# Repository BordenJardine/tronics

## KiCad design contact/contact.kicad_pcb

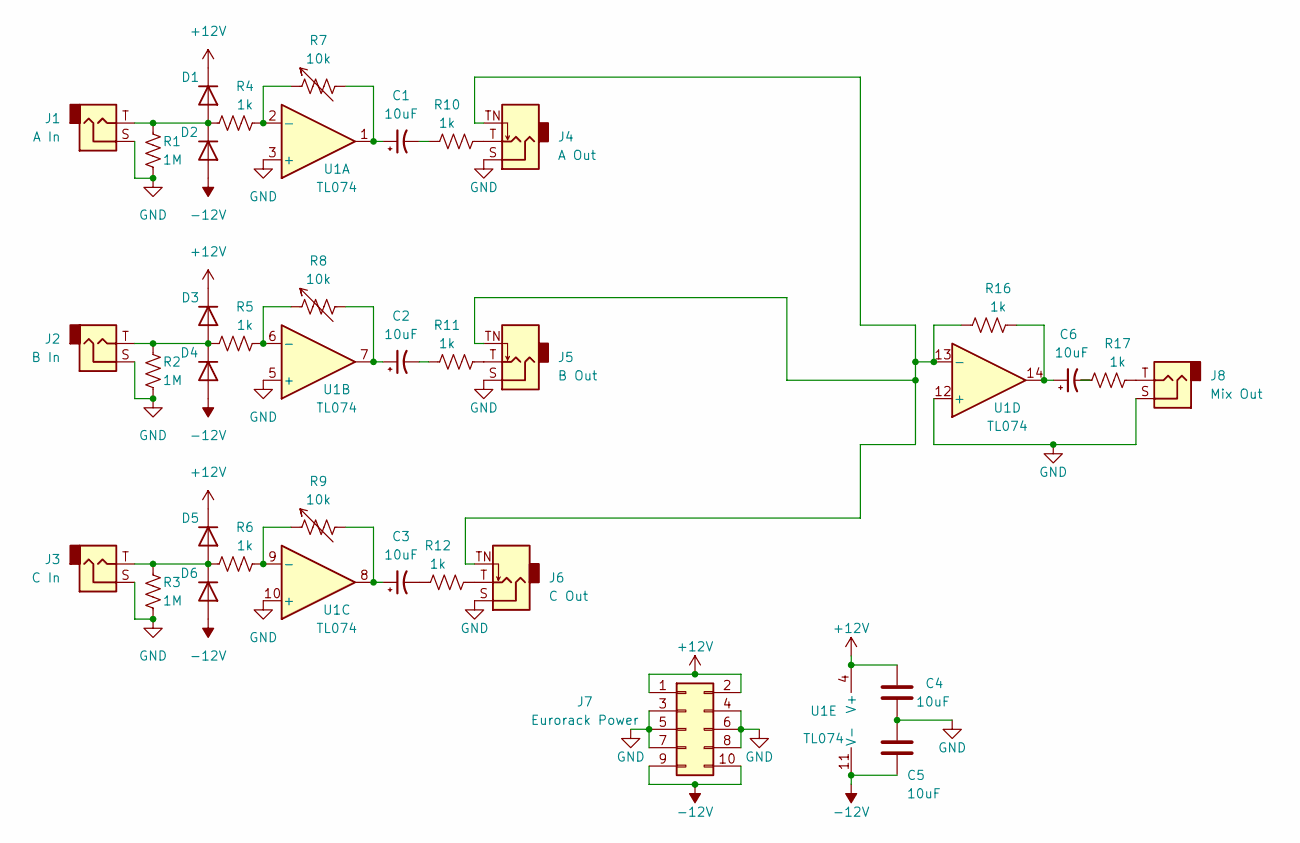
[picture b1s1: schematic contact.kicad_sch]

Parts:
C1, C2, C3, C6: 10uF; CP_Radial_D4.0mm_P1.50mm
C4, C5: 10uF; C_Rect_L10.0mm_W2.5mm_P7.50mm_MKS4
D1, D2, D3, D4, D5, D6: D; D_A-405_P7.62mm_Horizontal
J1: A In; Jack_3.5mm_QingPu_WQP-PJ398SM_Vertical_CircularHoles
J2: B In; Jack_3.5mm_QingPu_WQP-PJ398SM_Vertical_CircularHoles
J3: C In; Jack_3.5mm_QingPu_WQP-PJ398SM_Vertical_CircularHoles
J4: A Out; Jack_3.5mm_QingPu_WQP-PJ398SM_Vertical_CircularHoles
J5: B Out; Jack_3.5mm_QingPu_WQP-PJ398SM_Vertical_CircularHoles
J6: C Out; Jack_3.5mm_QingPu_WQP-PJ398SM_Vertical_CircularHoles
J7: Eurorack Power; PinHeader_2x05_P2.54mm_Vertical
J8: Mix Out; Jack_3.5mm_QingPu_WQP-PJ398SM_Vertical_CircularHoles
R1, R2, R3: 1M; R_Axial_DIN0204_L3.6mm_D1.6mm_P1.90mm_Vertical
R4, R5, R6, R10, R11, R12, R16, R17: 1k; R_Axial_DIN0204_L3.6mm_D1.6mm_P1.90mm_Vertical
R7, R8, R9: 10k; Potentiometer_Alps_RK09L_Single_Vertical
U1: TL074; DIP-14_W7.62mm

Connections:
+12V: C4.1, D1.1 (K), D3.1 (K), D5.1 (K), J7.1, J7.2, U1.4 (V+)
-12V: C5.1, D2.2 (A), D4.2 (A), D6.2 (A), J7.9, J7.10, U1.11 (V-)
GND: C4.2, C5.2, J1.S, J2.S, J3.S, J4.S, J5.S, J6.S, J7.3, J7.4, J7.5, J7.6, J7.7, J7.8, J8.S, R1.1, R2.1, R3.1, U1.3 (+), U1.5 (+), U1.10 (+), U1.12 (+)
unnamed: C1.1, R7.2, U1.1
unnamed: C1.2, R10.1
unnamed: C2.1, R8.2, U1.7
unnamed: C2.2, R11.1
unnamed: C3.1, R9.2, U1.8
unnamed: C3.2, R12.1
unnamed: C6.1, R16.2, U1.14
unnamed: C6.2, R17.1
unnamed: D1.2 (A), D2.1 (K), J1.T, R1.2, R4.1
unnamed: D3.2 (A), D4.1 (K), J2.T, R2.2, R5.1
unnamed: D5.2 (A), D6.1 (K), J3.T, R3.2, R6.1
unnamed: J4.T, R10.2
unnamed: J5.T, R11.2
unnamed: J6.T, R12.2
unnamed: J8.T, R17.2
unnamed: R4.2, R7.1, U1.2 (-)
unnamed: R5.2, R8.1, U1.6 (-)
unnamed: R6.2, R9.1, U1.9 (-)
unnamed: J4.TN, J5.TN, J6.TN, R16.1, U1.13 (-)

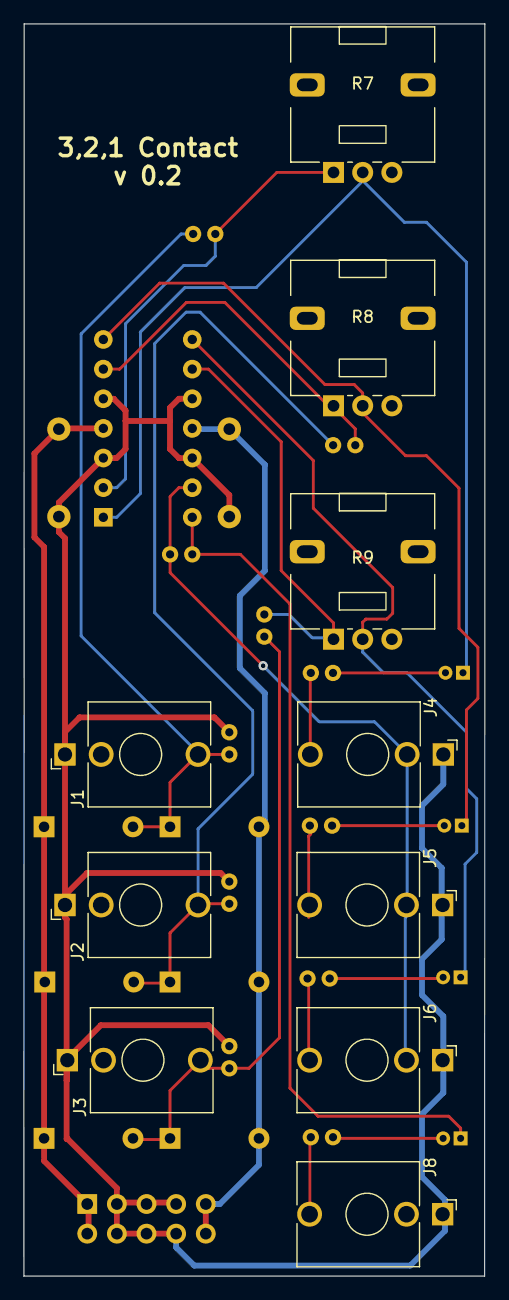
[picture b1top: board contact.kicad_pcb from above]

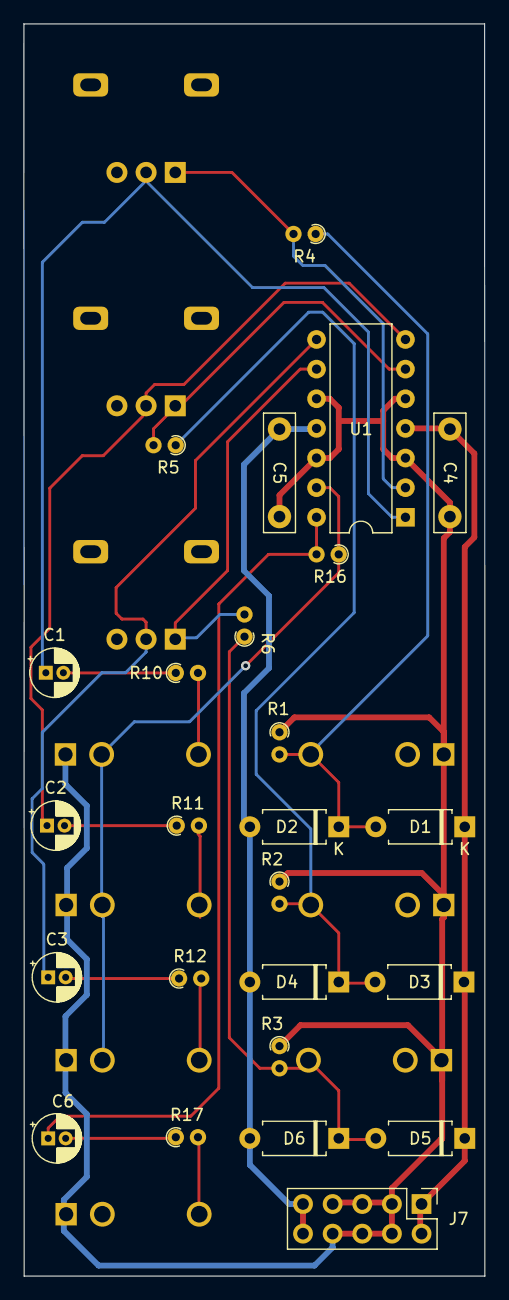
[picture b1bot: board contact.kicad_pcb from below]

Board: 2 copper layers, 39.5 x 107.3 mm, 35 parts (25 on the bottom side), 22 nets.

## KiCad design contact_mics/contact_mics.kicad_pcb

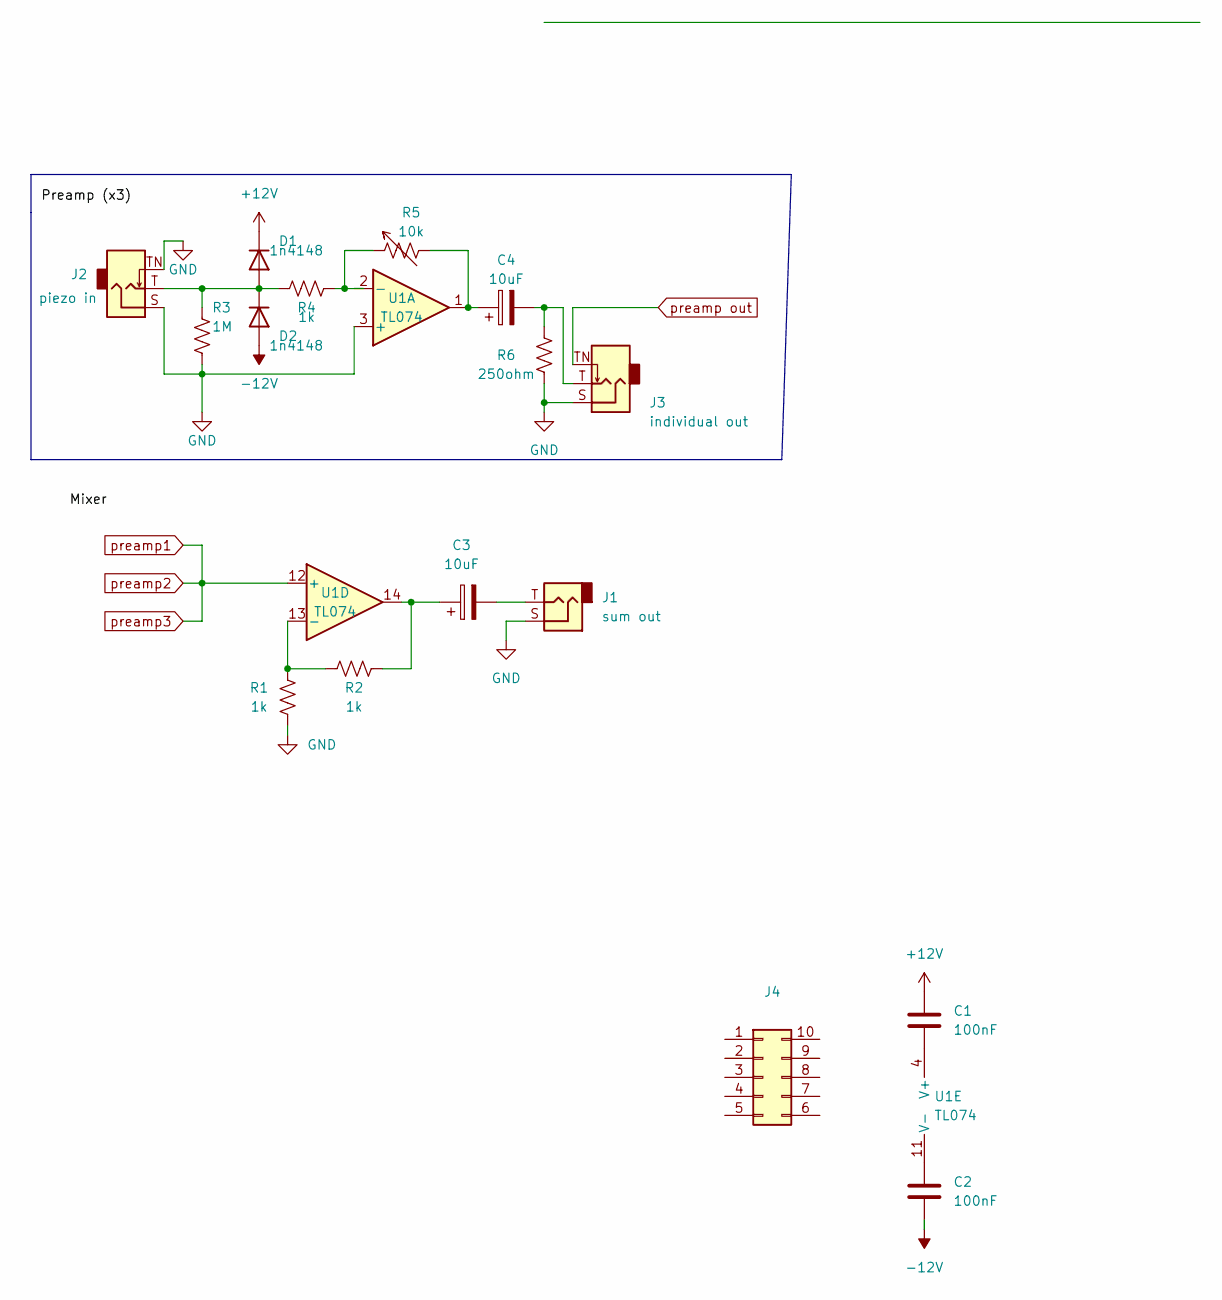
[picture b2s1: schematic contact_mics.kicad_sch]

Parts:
C1, C2: 100nF
C3, C4: 10uF
D1, D2: 1n4148
J1: sum out
J2: piezo in
J3: individual out
J4: (no value)
R1, R2, R4: 1k
R3: 1M
R5: 10k
R6: 250ohm
U1: TL074

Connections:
+12V: C1.1, D1.1 (K)
-12V: C2.2, D2.2 (A)
GND: J1.S, J2.S, J2.TN, J3.S, R1.2, R3.2, R6.2, U1.3 (+)
unnamed: C1.2, U1.4 (V+)
unnamed: C2.1, U1.11 (V-)
unnamed: C3.1, R2.2, U1.14
unnamed: C3.2, J1.T
unnamed: C4.1, R5.2, U1.1
unnamed: C4.2, J3.T, R6.1
unnamed: D1.2 (A), D2.1 (K), J2.T, R3.1, R4.1
unnamed: R1.1, R2.1, U1.13 (-)
unnamed: R4.2, R5.1
preamp1: U1.12 (+)
preamp out: J3.TN

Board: 2 copper layers, 16 parts (0 on the bottom side), 12 nets, no tracks yet.

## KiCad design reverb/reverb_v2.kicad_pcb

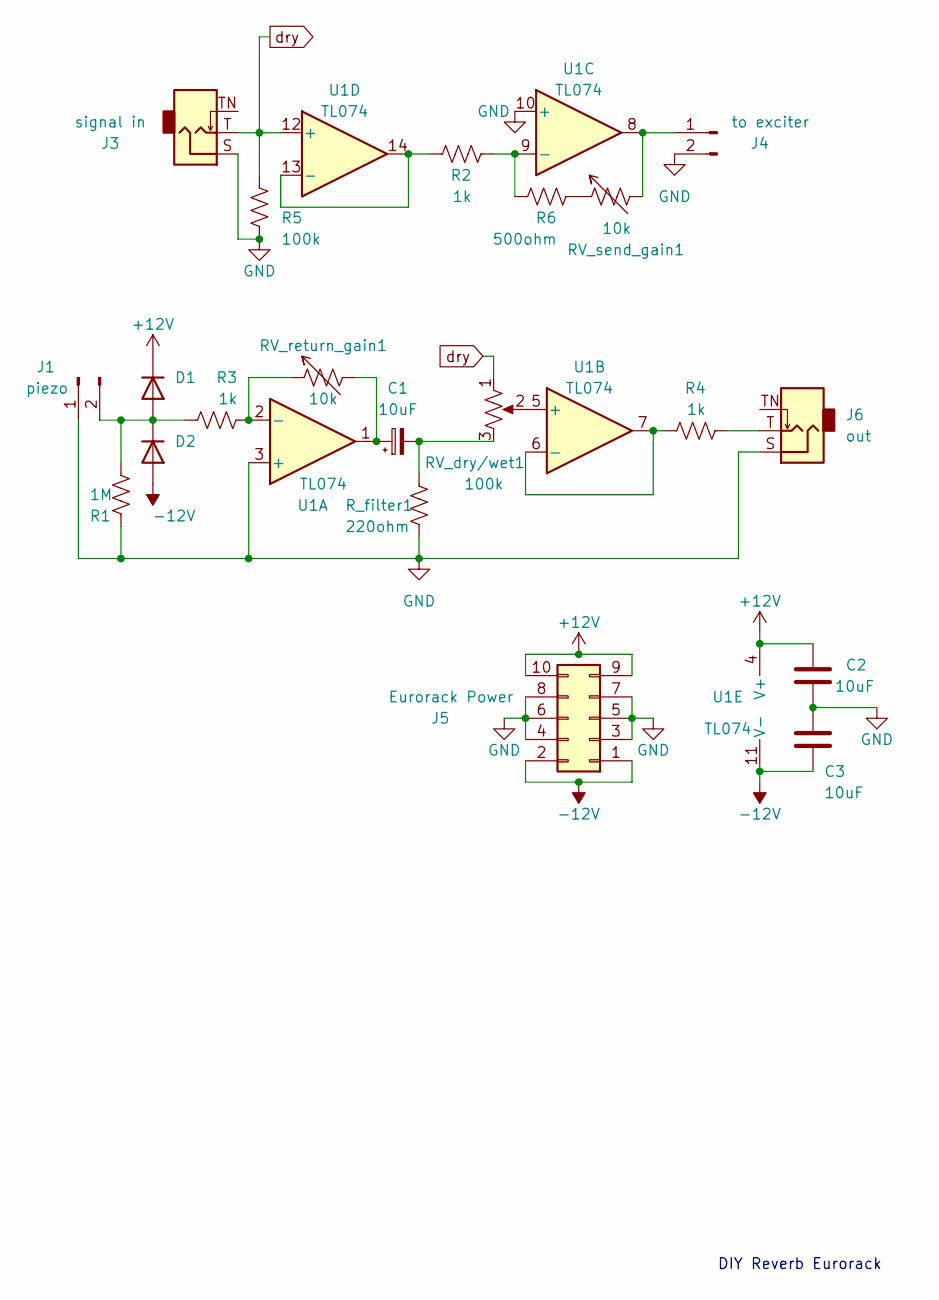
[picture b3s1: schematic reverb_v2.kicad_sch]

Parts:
C1: 10uF; CP_Radial_D5.0mm_P2.50mm
C2, C3: 10uF; C_Rect_L10.0mm_W2.5mm_P7.50mm_MKS4
D1, D2: D_A-405_P7.62mm_Horizontal
J1: piezo; PinHeader_1x02_P2.54mm_Vertical
J3: signal in; Jack_3.5mm_QingPu_WQP-PJ398SM_Vertical_CircularHoles
J4: to exciter; PinHeader_1x02_P2.54mm_Vertical
J5: Eurorack Power; PinHeader_2x05_P2.54mm_Vertical
J6: out; Jack_3.5mm_QingPu_WQP-PJ398SM_Vertical_CircularHoles
R1: 1M; R_Axial_DIN0207_L6.3mm_D2.5mm_P5.08mm_Vertical
R2, R3, R4: 1k; R_Axial_DIN0207_L6.3mm_D2.5mm_P5.08mm_Vertical
R5: 100k; R_Axial_DIN0207_L6.3mm_D2.5mm_P5.08mm_Vertical
R6: 500ohm; R_Axial_DIN0207_L6.3mm_D2.5mm_P5.08mm_Vertical
RV_dry/wet1: 100k; Potentiometer_Alps_RK09K_Single_Vertical
RV_return_gain1: 10k; Potentiometer_Alps_RK09K_Single_Vertical
RV_send_gain1: 10k; Potentiometer_Alps_RK09K_Single_Vertical
R_filter1: 220ohm; R_Axial_DIN0207_L6.3mm_D2.5mm_P5.08mm_Vertical
U1: TL074; DIP-14_W7.62mm

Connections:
+12V: C2.1, D1.1 (K), J5.9, J5.10, U1.4 (V+)
-12V: C3.1, D2.2 (A), J5.1, J5.2, U1.11 (V-)
GND: C2.2, C3.2, J1.1, J3.S, J4.2, J5.3, J5.4, J5.5, J5.6, J5.7, J5.8, J6.S, R1.2, R5.2, R_filter1.2, U1.3 (+), U1.10 (+)
unnamed: C1.1, RV_return_gain1.2, U1.1
unnamed: C1.2, RV_dry/wet1.3, R_filter1.1
unnamed: D1.2 (A), D2.1 (K), J1.2, R1.1, R3.1
unnamed: J6.T, R4.2
unnamed: R2.1, U1.13 (-), U1.14
unnamed: R2.2, R6.1, U1.9 (-)
unnamed: R3.2, RV_return_gain1.1, U1.2 (-)
unnamed: R4.1, U1.6 (-), U1.7
unnamed: R6.2, RV_send_gain1.1
unnamed: RV_dry/wet1.2, U1.5 (+)
unnamed: J4.1, RV_send_gain1.2, U1.8
dry: J3.T, R5.1, RV_dry/wet1.1, U1.12 (+)

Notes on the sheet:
DIY Reverb Eurorack

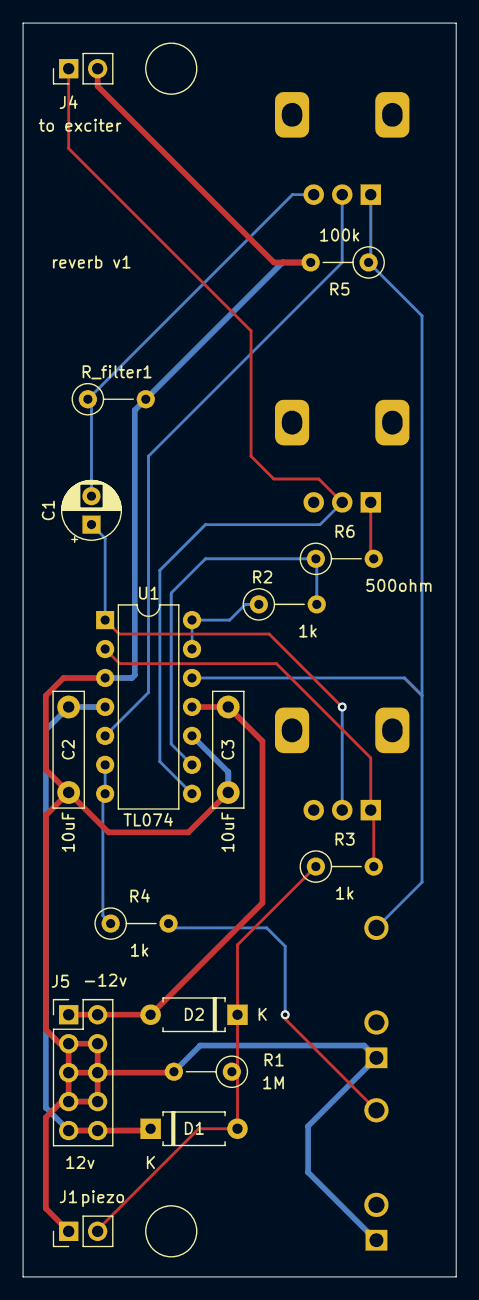
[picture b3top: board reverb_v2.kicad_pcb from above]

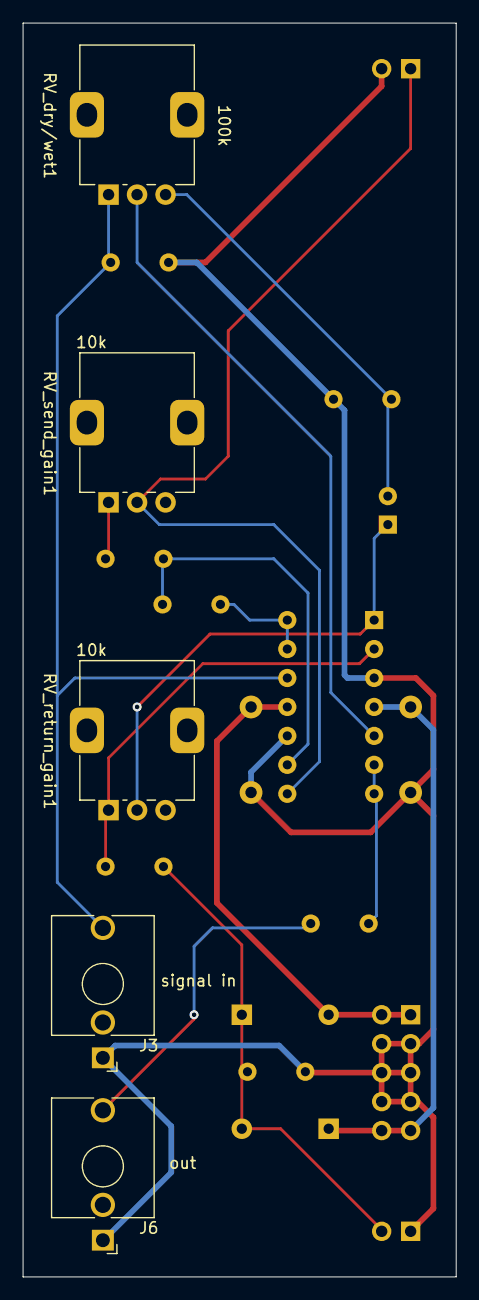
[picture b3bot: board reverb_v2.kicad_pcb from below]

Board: 2 copper layers, 38.0 x 110.0 mm, 21 parts (5 on the bottom side), 15 nets.

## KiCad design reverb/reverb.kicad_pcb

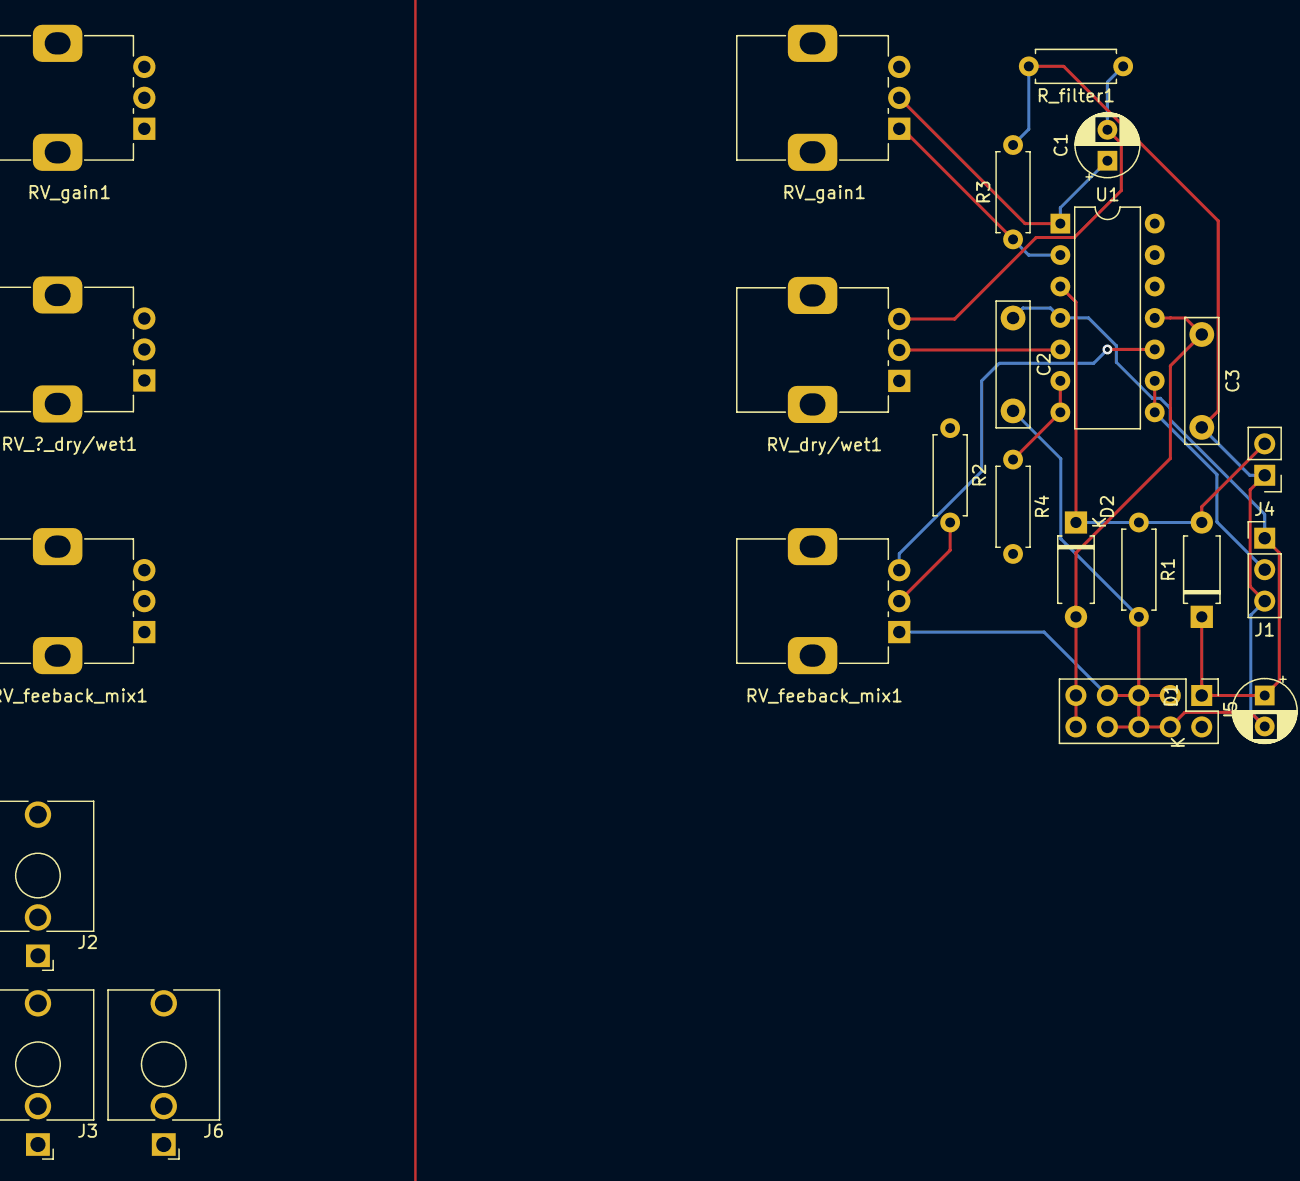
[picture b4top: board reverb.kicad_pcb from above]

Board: 2 copper layers, 24 parts (0 on the bottom side), 15 nets.

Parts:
C1: 10uF; CP_Radial_D5.0mm_P2.50mm
C2, C3: 10uF; C_Rect_L10.0mm_W2.5mm_P7.50mm_MKS4
C4: 100uF; CP_Radial_D5.0mm_P2.50mm
D1, D2: D; D_A-405_P7.62mm_Horizontal
J1: piezo; PinHeader_1x02_P2.54mm_Vertical
J2: feedback in; Jack_3.5mm_QingPu_WQP-PJ398SM_Vertical_CircularHoles
J3: signal in; Jack_3.5mm_QingPu_WQP-PJ398SM_Vertical_CircularHoles
J4: to exciter amp; PinHeader_1x03_P2.54mm_Vertical
J5: Eurorack Power; PinHeader_2x05_P2.54mm_Vertical
J6: out; Jack_3.5mm_QingPu_WQP-PJ398SM_Vertical_CircularHoles
R1: 1M; R_Axial_DIN0207_L6.3mm_D2.5mm_P7.62mm_Horizontal
R2: 10k; R_Axial_DIN0207_L6.3mm_D2.5mm_P7.62mm_Horizontal
R3, R4: 1k; R_Axial_DIN0207_L6.3mm_D2.5mm_P7.62mm_Horizontal
RV_?_dry/wet1: 100k; Potentiometer_Alps_RK09K_Single_Vertical
RV_dry/wet1: 100k; Potentiometer_Alps_RK09K_Single_Vertical
RV_feeback_mix1: 10k; Potentiometer_Alps_RK09K_Single_Vertical
RV_feeback_mix1#2: 100k; Potentiometer_Alps_RK09K_Single_Vertical
RV_gain1, RV_gain1#2: 10k; Potentiometer_Alps_RK09K_Single_Vertical
R_filter1: 220ohm; R_Axial_DIN0207_L6.3mm_D2.5mm_P7.62mm_Horizontal
U1: TL074; DIP-14_W7.62mm

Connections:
+12V: C2.1, C4.1, D1.1 (K), J4.1, J5.1, J5.2, U1.4 (V+)
-12V: C3.1, D2.2 (A), J5.9, J5.10, U1.11 (V-)
GND: C2.2, C3.2, C4.2, J1.1, J2.S, J3.S, J3.TN, J4.3, J5.3, J5.4, J5.5, J5.6, J5.7, J5.8, J6.S, J6.TN, R1.2, R3.2, RV_feeback_mix1#2.1, R_filter1.2
unnamed: C1.1, RV_gain1.2, U1.1
unnamed: C1.2, J2.TN, RV_dry/wet1.3, R_filter1.1
unnamed: D1.2 (A), D2.1 (K), J1.2, R1.1, U1.3 (+)
unnamed: J2.T, R2.1
unnamed: J3.T, RV_dry/wet1.1
unnamed: J4.2, U1.8, U1.9 (-)
unnamed: J6.T, R4.2
unnamed: R2.2, RV_feeback_mix1#2.2
unnamed: R3.1, RV_gain1.1, U1.2 (-)
unnamed: R4.1, U1.6 (-), U1.7
unnamed: RV_dry/wet1.2, U1.5 (+)
unnamed: RV_feeback_mix1#2.3, U1.10 (+)

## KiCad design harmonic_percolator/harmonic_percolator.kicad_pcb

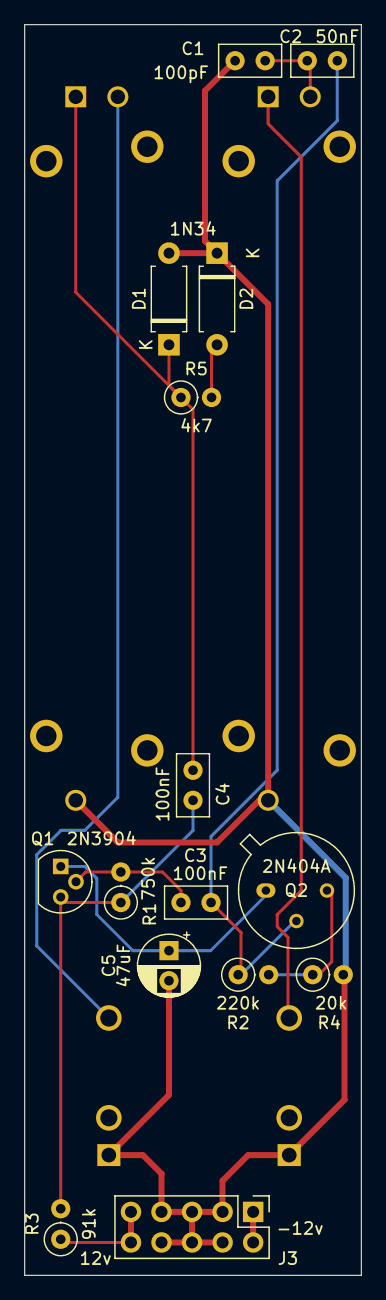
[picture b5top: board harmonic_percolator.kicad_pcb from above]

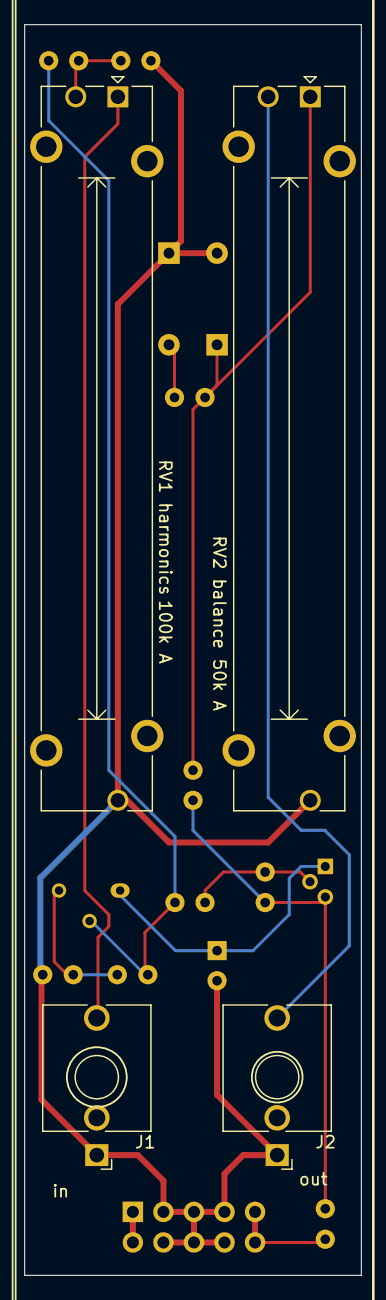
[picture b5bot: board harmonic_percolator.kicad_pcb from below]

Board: 2 copper layers, 28.0 x 104.0 mm, 19 parts (4 on the bottom side), 13 nets.

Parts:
C1: 100pF; C_Disc_D5.0mm_W2.5mm_P2.50mm
C2: 50nF; C_Disc_D5.0mm_W2.5mm_P2.50mm
C3, C4: 100nF; C_Disc_D5.0mm_W2.5mm_P2.50mm
C5: 47uF; CP_Radial_D5.0mm_P2.50mm
D1, D2: 1N34; D_A-405_P7.62mm_Horizontal
J1: in; Jack_3.5mm_QingPu_WQP-PJ398SM_Vertical_CircularHoles
J2: out; Jack_3.5mm_QingPu_WQP-PJ398SM_Vertical_CircularHoles
J3: Eurorack Power; PinHeader_2x05_P2.54mm_Vertical
Q1: 2N3904; TO-92
Q2: 2N404A; TO-5-3
R1: 750k; R_Axial_DIN0207_L6.3mm_D2.5mm_P2.54mm_Vertical
R2: 220k; R_Axial_DIN0207_L6.3mm_D2.5mm_P2.54mm_Vertical
R3: 91k; R_Axial_DIN0207_L6.3mm_D2.5mm_P2.54mm_Vertical
R4: 20k; R_Axial_DIN0207_L6.3mm_D2.5mm_P2.54mm_Vertical
R5: 4k7; R_Axial_DIN0207_L6.3mm_D2.5mm_P2.54mm_Vertical
RV1 harmonics : 100k A; Potentiometer_Bourns_PTA4543_Single_Slide
RV2 balance: 50k A; Potentiometer_Bourns_PTA4543_Single_Slide

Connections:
+12V: J3.9, J3.10, R3.1
-12V: J3.1, J3.2
GND: C1.2, C5.2, D1.2 (A), D2.1 (K), J1.S, J2.S, J3.3, J3.4, J3.5, J3.6, J3.7, J3.8, R4.2, RV1 harmonics.3, RV2 balance.3
unnamed: C1.1, C2.2, RV1 harmonics.2
unnamed: C2.1, C3.2, Q2.2 (B), R2.1
unnamed: C3.1, Q1.2 (B), R1.2
unnamed: C4.1, D1.1 (K), R5.1, RV2 balance.1
unnamed: C4.2, Q1.3 (C), R1.1, R3.2
unnamed: C5.1, Q1.1 (E), Q2.1 (E)
unnamed: D2.2 (A), R5.2
unnamed: J1.T, RV1 harmonics.1
unnamed: J2.T, RV2 balance.2
unnamed: Q2.3 (C), R2.2, R4.1

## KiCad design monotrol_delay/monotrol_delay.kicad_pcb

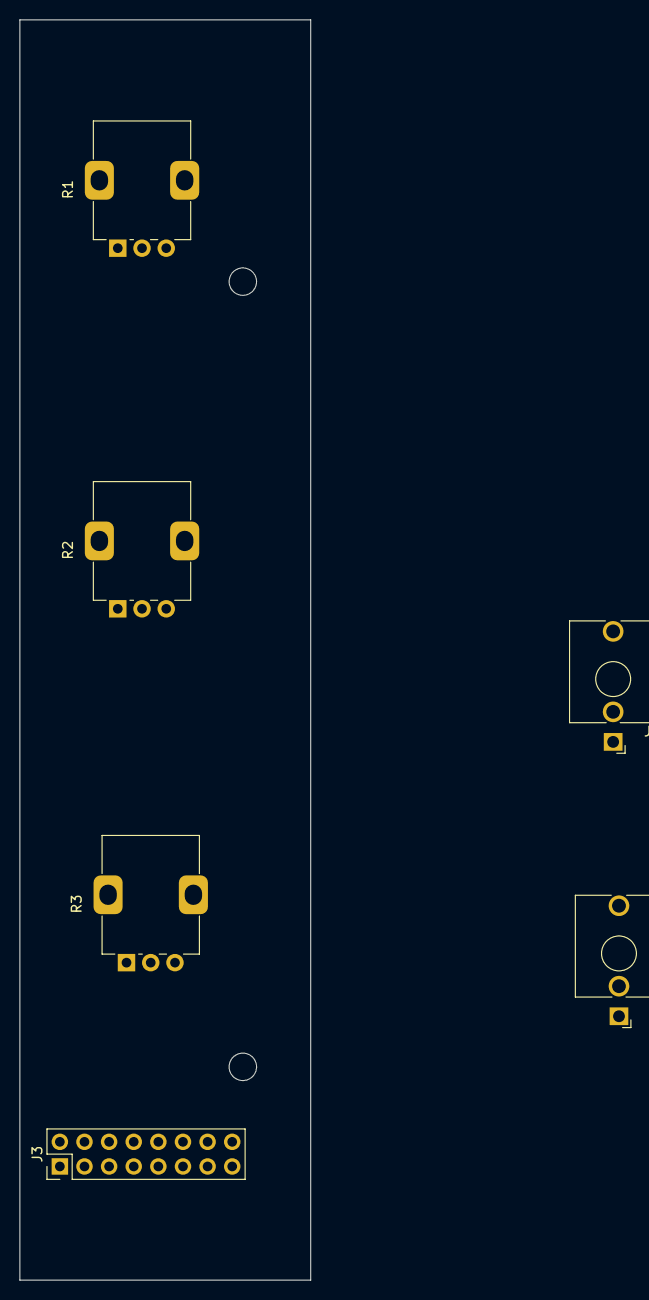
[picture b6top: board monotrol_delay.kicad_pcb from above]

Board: 2 copper layers, 30.0 x 130.0 mm, 6 parts (0 on the bottom side), 4 nets, no tracks yet.

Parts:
J1: in; Jack_3.5mm_QingPu_WQP-PJ398SM_Vertical_CircularHoles
J2: out; Jack_3.5mm_QingPu_WQP-PJ398SM_Vertical_CircularHoles
J3: Eurorack Power; PinHeader_2x08_P2.54mm_Vertical
R1: Q 10k; Potentiometer_Alps_RK09K_Single_Vertical
R2: T 100k; Potentiometer_Alps_RK09K_Single_Vertical
R3: FB 10k; Potentiometer_Alps_RK09K_Single_Vertical

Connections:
+5V: J3.11, J3.12
+12V: J3.9, J3.10
-12V: J3.1, J3.2
GND: J3.3, J3.4, J3.5, J3.6, J3.7, J3.8

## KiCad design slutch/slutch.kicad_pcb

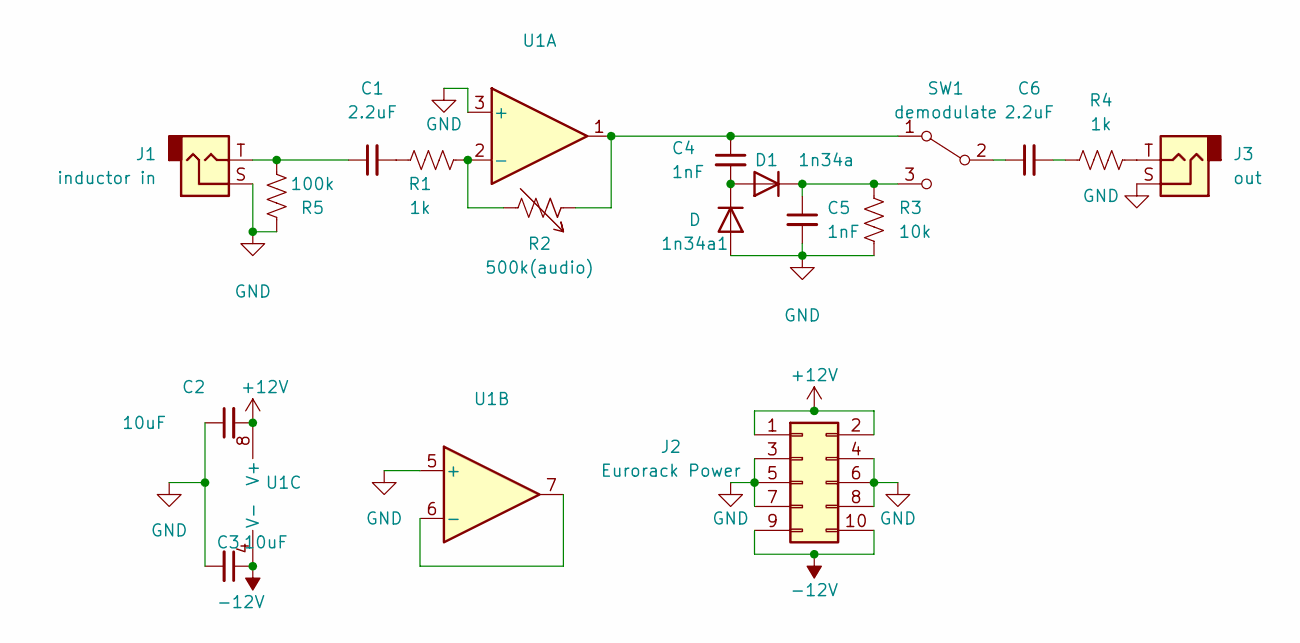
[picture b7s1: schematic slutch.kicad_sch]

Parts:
1n34a1: D; D_A-405_P7.62mm_Horizontal
C1, C6: 2.2uF; C_Disc_D5.0mm_W2.5mm_P5.00mm
C2, C3: 10uF; C_Rect_L7.0mm_W2.0mm_P5.00mm
C4, C5: 1nF; C_Disc_D5.0mm_W2.5mm_P5.00mm
D1: 1n34a; D_A-405_P7.62mm_Horizontal
J1: inductor in; Jack_3.5mm_QingPu_WQP-PJ398SM_Vertical_CircularHoles
J2: Eurorack Power; PinHeader_2x05_P2.54mm_Vertical
J3: out; Jack_3.5mm_QingPu_WQP-PJ398SM_Vertical_CircularHoles
R1, R4: 1k; R_Axial_DIN0204_L3.6mm_D1.6mm_P1.90mm_Vertical
R2: 500k(audio); Potentiometer_Alps_RK09K_Single_Vertical
R3: 10k; R_Axial_DIN0204_L3.6mm_D1.6mm_P1.90mm_Vertical
R5: 100k; R_Axial_DIN0204_L3.6mm_D1.6mm_P1.90mm_Vertical
SW1: demodulate; SW_Slide_1P2T_CK_OS102011MS2Q
U1: (no value)

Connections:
+12V: C2.2, J2.1, J2.2, U1.8 (V+)
-12V: C3.1, J2.9, J2.10, U1.4 (V-)
GND: 1n34a1.2 (A), C2.1, C3.2, C5.2, J1.S, J2.3, J2.4, J2.5, J2.6, J2.7, J2.8, J3.S, R3.2, R5.2, U1.3 (+), U1.5 (+)
unnamed: 1n34a1.1 (K), C4.2, D1.2 (A)
unnamed: C1.1, J1.T, R5.1
unnamed: C1.2, R1.1
unnamed: C4.1, R2.1, SW1.1 (A), U1.1
unnamed: C5.1, D1.1 (K), R3.1, SW1.3 (C)
unnamed: C6.1, SW1.2 (B)
unnamed: C6.2, R4.1
unnamed: J3.T, R4.2
unnamed: R1.2, R2.2, U1.2 (-)
unnamed: U1.6 (-), U1.7

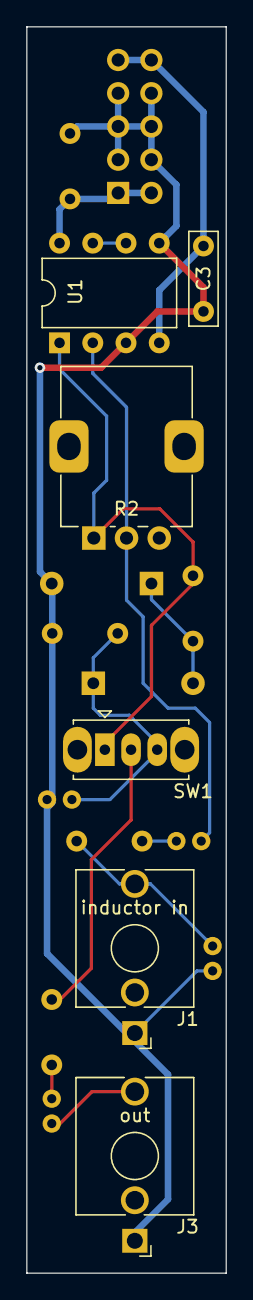
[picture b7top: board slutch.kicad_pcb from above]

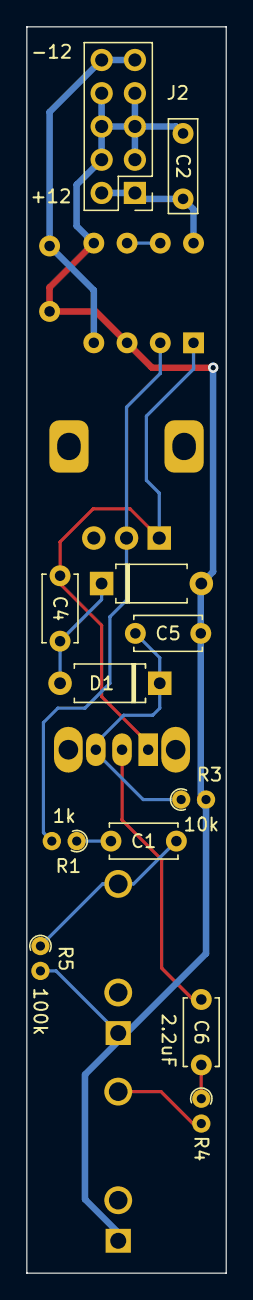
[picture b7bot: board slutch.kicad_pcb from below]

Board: 2 copper layers, 15.2 x 95.2 mm, 18 parts (12 on the bottom side), 13 nets.

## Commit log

2023-11-25 tronics
